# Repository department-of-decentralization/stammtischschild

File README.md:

# DOD Stammtischschild

Fabrication files for the DOD Stammtisch sign.

Inspired by the [c-base/stammtischschild](https://github.com/c-base/stammtischschild).
Main differences:
- use visicut over fengrave
- no battery, just USB-C
- no ESP, just colored LEDs
- KISS

Contents:
- [visicut/](./visicut): laser engraving of the DOD wolpy
- [kicad/](./kicad): schematics, footprints, and pcb design

The afk-screenshot above shows an early production prototype (with USB-C breakout).

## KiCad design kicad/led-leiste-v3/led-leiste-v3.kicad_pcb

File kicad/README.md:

# PCB Manufacturing

KiCad project for the Stammtischschild containing schematics, footprints and final PCB design.

Gerber and drill files are in `fabrication-outputs/` subdirectory.

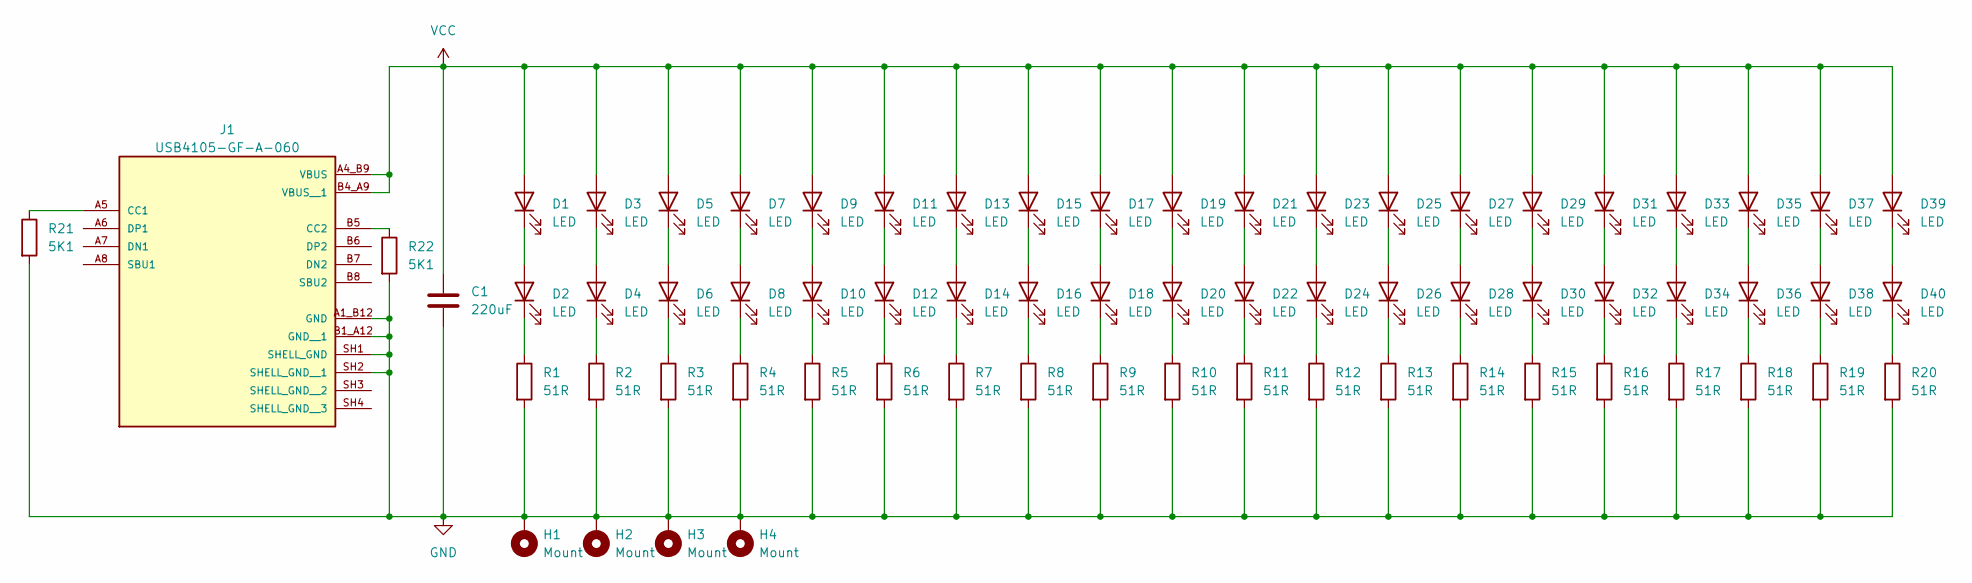
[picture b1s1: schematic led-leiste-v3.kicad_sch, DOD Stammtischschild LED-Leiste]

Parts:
C1: 220uF; C_1206_3216Metric
D1, D2, D3, D4, D5, D6, D7, D8, D9, D10, D11, D12, D13, D14, D15, D16, D17, D18, D19, D20, D21, D22, D23, D24, D25, D26, D27, D28, D29, D30, D31, D32, D33, D34, D35, D36, D37, D38, D39, D40: LED; LED_1206_3216Metric
H1, H2, H3, H4: Mount; MountingHole_2.7mm_M2.5_ISO14580_Pad
J1: USB4105-GF-A-060; GCT_USB4105-GF-A-060; PARTREV B3
R1, R2, R3, R4, R5, R6, R7, R8, R9, R10, R11, R12, R13, R14, R15, R16, R17, R18, R19, R20: 51R; R_1206_3216Metric
R21, R22: 5K1; R_1206_3216Metric

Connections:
GND: C1.2, H1.1, H2.1, H3.1, H4.1, J1.A1_B12 (GND), J1.B1_A12 (GND__1), J1.SH1 (SHELL_GND), J1.SH2 (SHELL_GND__1), R1.2, R2.2, R3.2, R4.2, R5.2, R6.2, R7.2, R8.2, R9.2, R10.2, R11.2, R12.2, R13.2, R14.2, R15.2, R16.2, R17.2, R18.2, R19.2, R20.2, R21.2, R22.2
unnamed: D1.1 (K), D2.2 (A)
unnamed: D2.1 (K), R1.1
unnamed: D3.1 (K), D4.2 (A)
unnamed: D4.1 (K), R2.1
unnamed: D5.1 (K), D6.2 (A)
unnamed: D6.1 (K), R3.1
unnamed: D7.1 (K), D8.2 (A)
unnamed: D8.1 (K), R4.1
unnamed: D9.1 (K), D10.2 (A)
unnamed: D10.1 (K), R5.1
unnamed: D11.1 (K), D12.2 (A)
unnamed: D12.1 (K), R6.1
unnamed: D13.1 (K), D14.2 (A)
unnamed: D14.1 (K), R7.1
unnamed: D15.1 (K), D16.2 (A)
unnamed: D16.1 (K), R8.1
unnamed: D17.1 (K), D18.2 (A)
unnamed: D18.1 (K), R9.1
unnamed: D19.1 (K), D20.2 (A)
unnamed: D20.1 (K), R10.1
unnamed: D21.1 (K), D22.2 (A)
unnamed: D22.1 (K), R11.1
unnamed: D23.1 (K), D24.2 (A)
unnamed: D24.1 (K), R12.1
unnamed: D25.1 (K), D26.2 (A)
unnamed: D26.1 (K), R13.1
unnamed: D27.1 (K), D28.2 (A)
unnamed: D28.1 (K), R14.1
unnamed: D29.1 (K), D30.2 (A)
unnamed: D30.1 (K), R15.1
unnamed: D31.1 (K), D32.2 (A)
unnamed: D32.1 (K), R16.1
unnamed: D33.1 (K), D34.2 (A)
unnamed: D34.1 (K), R17.1
unnamed: D35.1 (K), D36.2 (A)
unnamed: D36.1 (K), R18.1
unnamed: D37.1 (K), D38.2 (A)
unnamed: D38.1 (K), R19.1
unnamed: D39.1 (K), D40.2 (A)
unnamed: D40.1 (K), R20.1
unnamed: J1.A5 (CC1), R21.1
unnamed: J1.B5 (CC2), R22.1
VCC: C1.1, D1.2 (A), D3.2 (A), D5.2 (A), D7.2 (A), D9.2 (A), D11.2 (A), D13.2 (A), D15.2 (A), D17.2 (A), D19.2 (A), D21.2 (A), D23.2 (A), D25.2 (A), D27.2 (A), D29.2 (A), D31.2 (A), D33.2 (A), D35.2 (A), D37.2 (A), D39.2 (A), J1.A4_B9 (VBUS), J1.B4_A9 (VBUS__1)

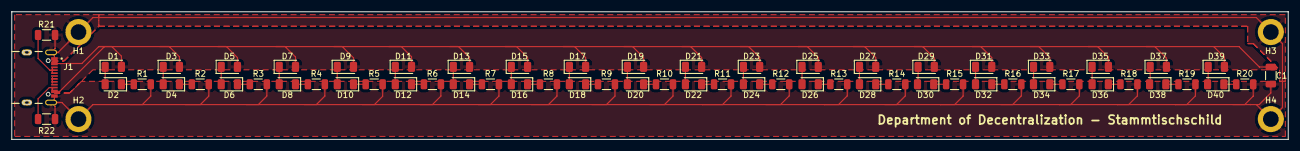
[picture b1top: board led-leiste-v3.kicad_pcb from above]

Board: 2 copper layers, 220.0 x 22.0 mm, 68 parts (0 on the bottom side), 44 nets.

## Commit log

2025-04-21 add screenshot
2025-04-21 add visicut laser engraving files
2025-04-21 add kicad schematics and pcb design
2025-04-21 kicad: provide gct usb4105 type-c footprint
